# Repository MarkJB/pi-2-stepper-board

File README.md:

Copyright 2016 Mark Benson. Portions probably copyright Raspberry Pi foundation (https://github.com/raspberrypi/hats) (Specifically the HAT Spec I2C EEPROM & Back-feed circuits) so I'm not attempting to assert any Copyright over them, besides my work is licensed under Creative Commons so not sure what else I can do. I'm not a lawyer... thinking about this stuff makes my brain ache.

License: CC-BY 4.0

No warranty implied or given. Use at your own risk.

Repo branches:

Master is at v1.01b

PCBs in the wild (4) at v1.0b

* v1.0a - Pi 2/3 add-on board. Original version.
* v1.0b - Pi 2/3 HAT spec capable board. PCB follows the Pi Foundation HAT spec https://github.com/raspberrypi/hats
* v1.01b - Fixes - Swapped com port pins (Pi Tx/Rx now nearest GPIO and Arduino Tx/Rx nearest Arduino as that seems more logical) - Changed LED for Bi-colour LED, uses existing LED GPIO Pin 7 (GP4) and adds Pin 17 (GP17) - Removed plating from NTPH camera slot - Fixed front silk screen Endstop2 graphic line now points to P3.

###This is my Pi 'HAT'* drawing machine add-on board for the Raspberry Pi 2 (and later).

It can drive 2 stepper motors and a servo, has provision for end stop switches and both I2C and SPI peripherals.

Designed for use with vPiP (https://github.com/brianinnes/vpip). vPiP is a Python based vertical hanging plotter control software.

This board is a work in progress and is currently untested.

vPiP is as yet unreleased. More information as it becomes available.

I wouldn't bother making one yet...

\* 'HAT' because while the board supports the HAT spec, it would have to be assembled with the HAT spec components (the EEPROM would need to be programmed, plus a few other pyhsical additions like a specific height GPIO connector and stand-offs) to be considered a HAT without any reservations.

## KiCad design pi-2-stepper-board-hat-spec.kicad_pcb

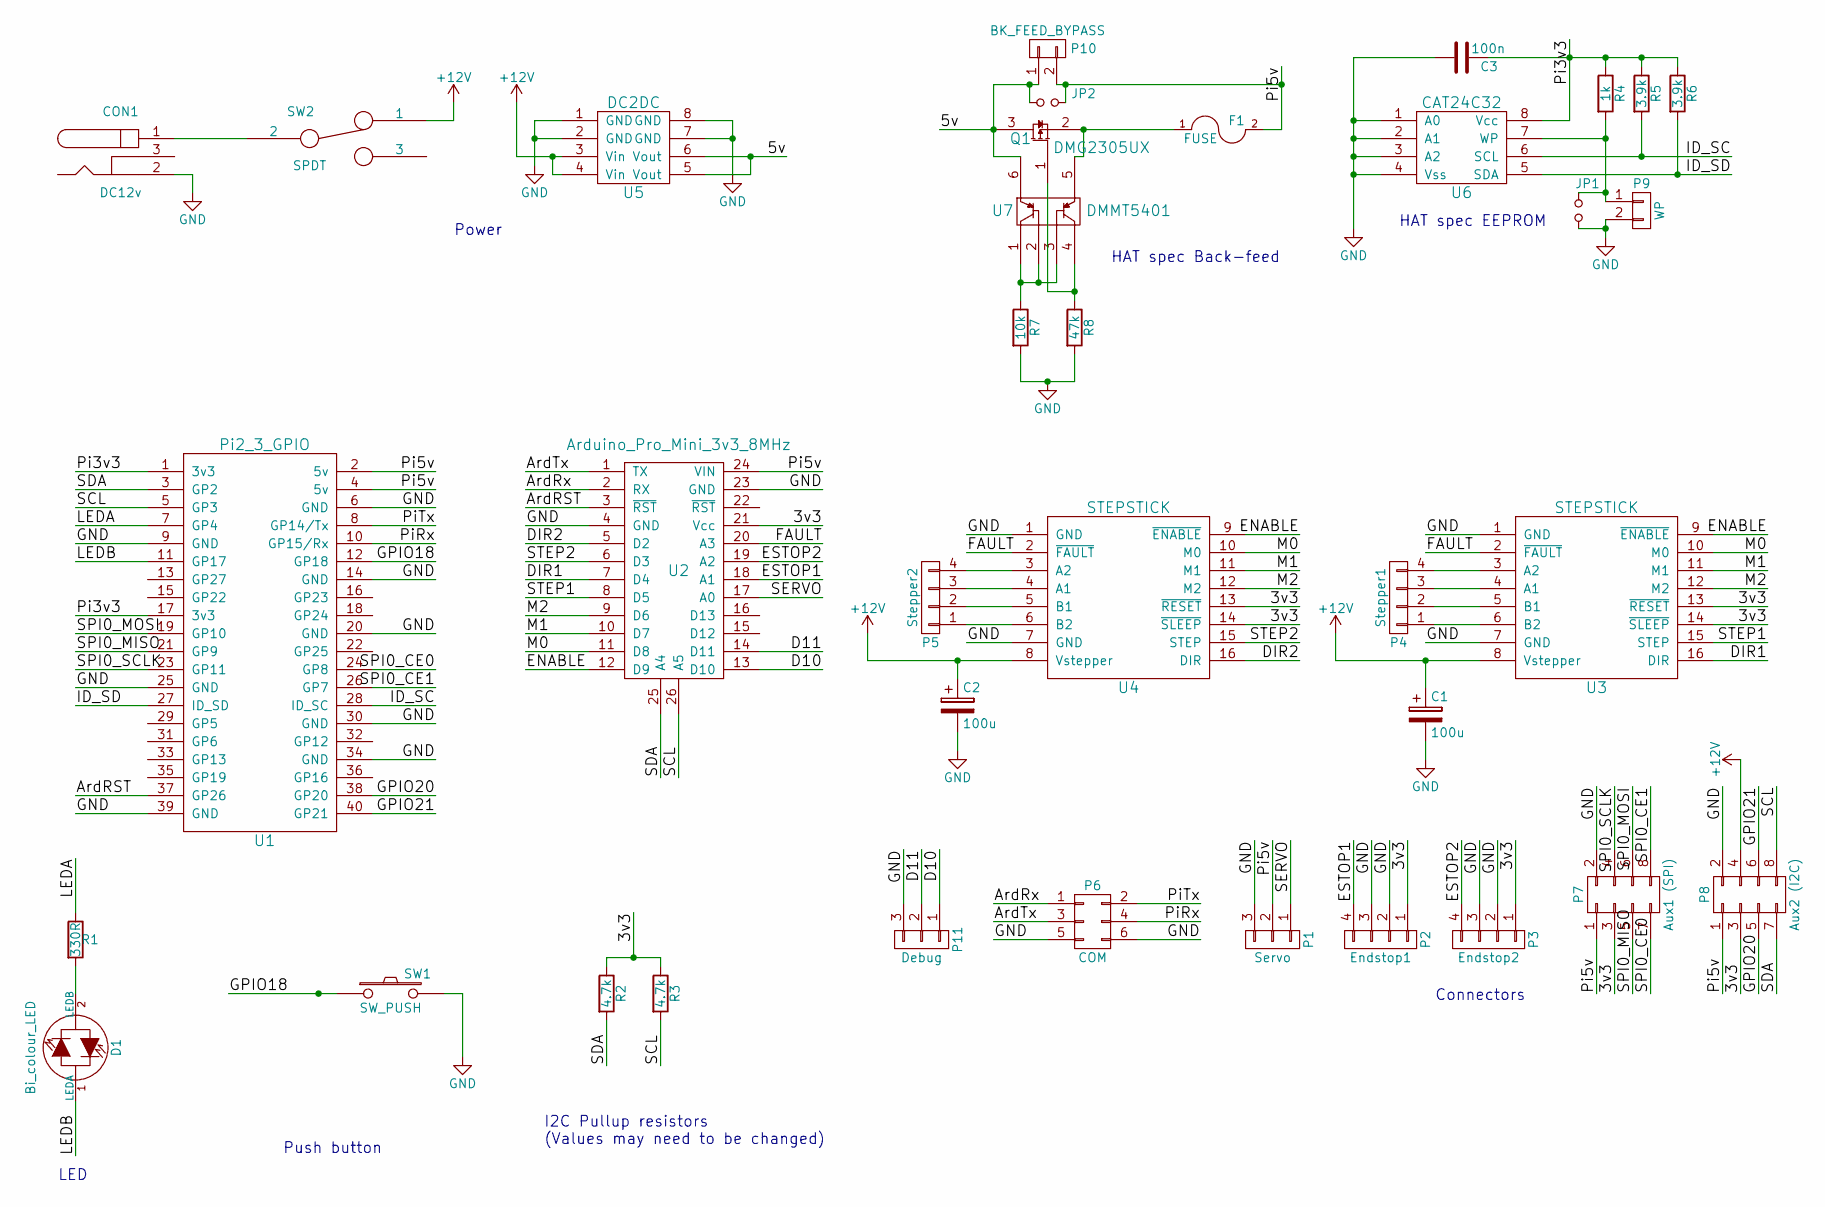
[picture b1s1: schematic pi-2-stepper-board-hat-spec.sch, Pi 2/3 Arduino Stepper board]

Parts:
C1, C2: 100u; Cap_laying_flat_2.5mm_lead_pitch
C3: 100n; C_0805
CON1: DC12v; BARREL_JACK
D1: Bi_colour_LED; LED-3MM
F1: FUSE; Fuse_SMD1206_HandSoldering
JP1, JP2: Jumper_NO_Small; Solder_Jumper
P1: Servo; Pin_Header_Straight_1x03
P2: Endstop1; Pin_Header_Straight_1x04
P3: Endstop2; Pin_Header_Straight_1x04
P4: Stepper1; Pin_Header_Straight_1x04
P5: Stepper2; Pin_Header_Straight_1x04
P6: COM; Pin_Header_Straight_2x03
P7: Aux1 (SPI); Pin_Header_Straight_2x04
P8: Aux2 (I2C); Pin_Header_Straight_2x04
P9: WP; Pin_Header_Straight_1x02
P10: BK_FEED_BYPASS; Pin_Header_Straight_1x02
P11: Debug; Pin_Header_Straight_1x03
Q1: DMG2305UX; SOT-23
R1: 330R; R1
R2, R3: 4.7k; R_0805
R4: 1k; R_0805
R5, R6: 3.9k; R_0805
R7: 10k; R_0805
R8: 47k; R_0805
SW1: SW_PUSH; TactSw
SW2: SPDT; SlideSw
U1: Pi2_3_GPIO; Pi_2_3_Hat_spec
U2: Arduino_Pro_Mini_3v3_8MHz; Arduino_Pro_Mini
U3, U4: STEPSTICK; Stepstick
U5: DC2DC; DSUN_DC2DC
U6: CAT24C32; SOIC-8_3.9x4.9mm_Pitch1.27mm
U7: DMMT5401; SOT-23-6

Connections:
+12V: C1.1, C2.1, P8.4, SW2.1, U3.8 (Vstepper), U4.8 (Vstepper), U5.3 (Vin), U5.4 (Vin)
/3v3: P2.1, P3.1, P7.3, P8.3, R2.1, R3.1, U2.21 (Vcc), U3.13 (~RESET), U3.14 (~SLEEP), U4.13 (~RESET), U4.14 (~SLEEP)
/ArdRST: U1.37 (GP26), U2.3 (~RST)
/ArdRx: P6.1, U2.2 (RX)
/ArdTx: P6.3, U2.1 (TX)
/D10: P11.1, U2.13 (D10)
/D11: P11.2, U2.14 (D11)
/DIR1: U2.7 (D4), U3.16 (DIR)
/DIR2: U2.5 (D2), U4.16 (DIR)
/ENABLE: U2.12 (D9), U3.9 (~ENABLE), U4.9 (~ENABLE)
/ESTOP1: P2.4, U2.18 (A1)
/ESTOP2: P3.4, U2.19 (A2)
/FAULT: U2.20 (A3), U3.2 (~FAULT), U4.2 (~FAULT)
/GPIO18: SW1.1, U1.12 (GP18)
/GPIO20: P8.5, U1.38 (GP20)
/GPIO21: P8.6, U1.40 (GP21)
/ID_SC: R5.2, U1.28 (ID_SC), U6.6 (SCL)
/ID_SD: R6.2, U1.27 (ID_SD), U6.5 (SDA)
/LEDA: R1.1, U1.7 (GP4)
/LEDB: D1.1 (LEDA), U1.11 (GP17)
/M0: U2.11 (D8), U3.10 (M0), U4.10 (M0)
/M1: U2.10 (D7), U3.11 (M1), U4.11 (M1)
/M2: U2.9 (D6), U3.12 (M2), U4.12 (M2)
/Pi3v3: C3.1, R4.1, R5.1, R6.1, U1.1 (3v3), U1.17 (3v3), U6.8 (Vcc)
/Pi5v: F1.2, JP2.2, P1.2, P7.1, P8.1, P10.2, U1.2 (5v), U1.4 (5v), U2.24 (VIN)
/PiRx: P6.4, U1.10 (GP15/Rx)
/PiTx: P6.2, U1.8 (GP14/Tx)
/SCL: P8.8, R3.2, U1.5 (GP3), U2.26 (A5)
/SDA: P8.7, R2.2, U1.3 (GP2), U2.25 (A4)
/SERVO: P1.1, U2.17 (A0)
/SPI0_CE0: P7.7, U1.24 (GP8)
/SPI0_CE1: P7.8, U1.26 (GP7)
/SPI0_MISO: P7.5, U1.21 (GP9)
/SPI0_MOSI: P7.6, U1.19 (GP10)
/SPI0_SCLK: P7.4, U1.23 (GP11)
/STEP1: U2.8 (D5), U3.15 (STEP)
/STEP2: U2.6 (D3), U4.15 (STEP)
unnamed: CON1.1, SW2.2
unnamed: D1.2 (LEDB), R1.2
unnamed: F1.1, Q1.2, U7.5
unnamed: JP1.1, P9.1, R4.2, U6.7 (WP)
unnamed: P4.1, U3.6 (B2)
unnamed: P4.2, U3.5 (B1)
unnamed: P4.3, U3.4 (A1)
unnamed: P4.4, U3.3 (A2)
unnamed: P5.1, U4.6 (B2)
unnamed: P5.2, U4.5 (B1)
unnamed: P5.3, U4.4 (A1)
unnamed: P5.4, U4.3 (A2)
unnamed: Q1.1, R8.1, U7.4
unnamed: R7.1, U7.1, U7.2, U7.3

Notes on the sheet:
Push button
I2C Pullup resistors (Values may need to be changed)
Power
Connectors
HAT spec EEPROM
LED
HAT spec Back-feed

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
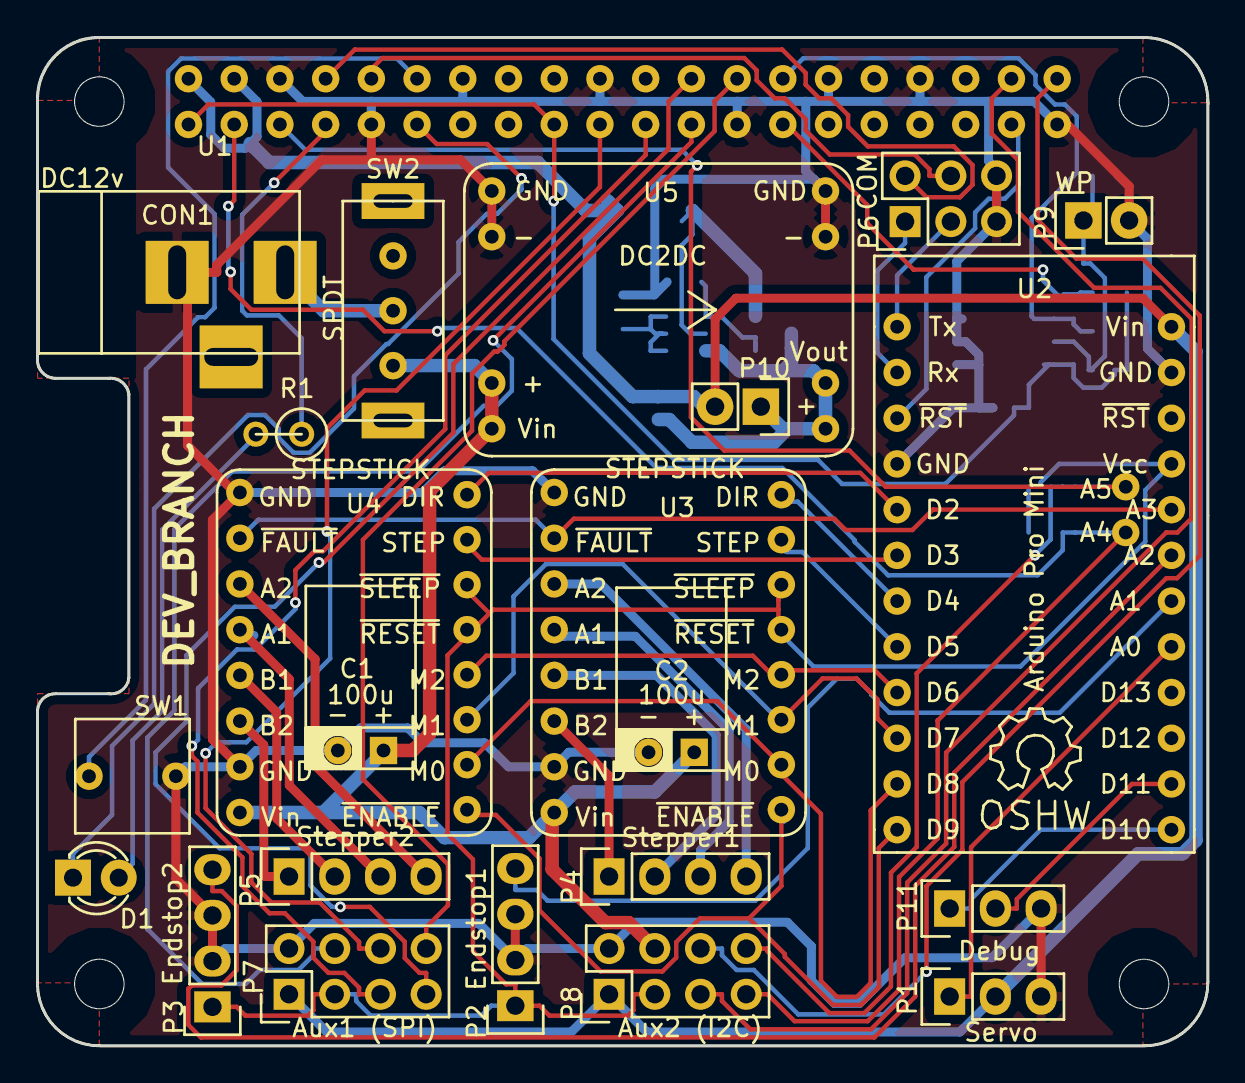
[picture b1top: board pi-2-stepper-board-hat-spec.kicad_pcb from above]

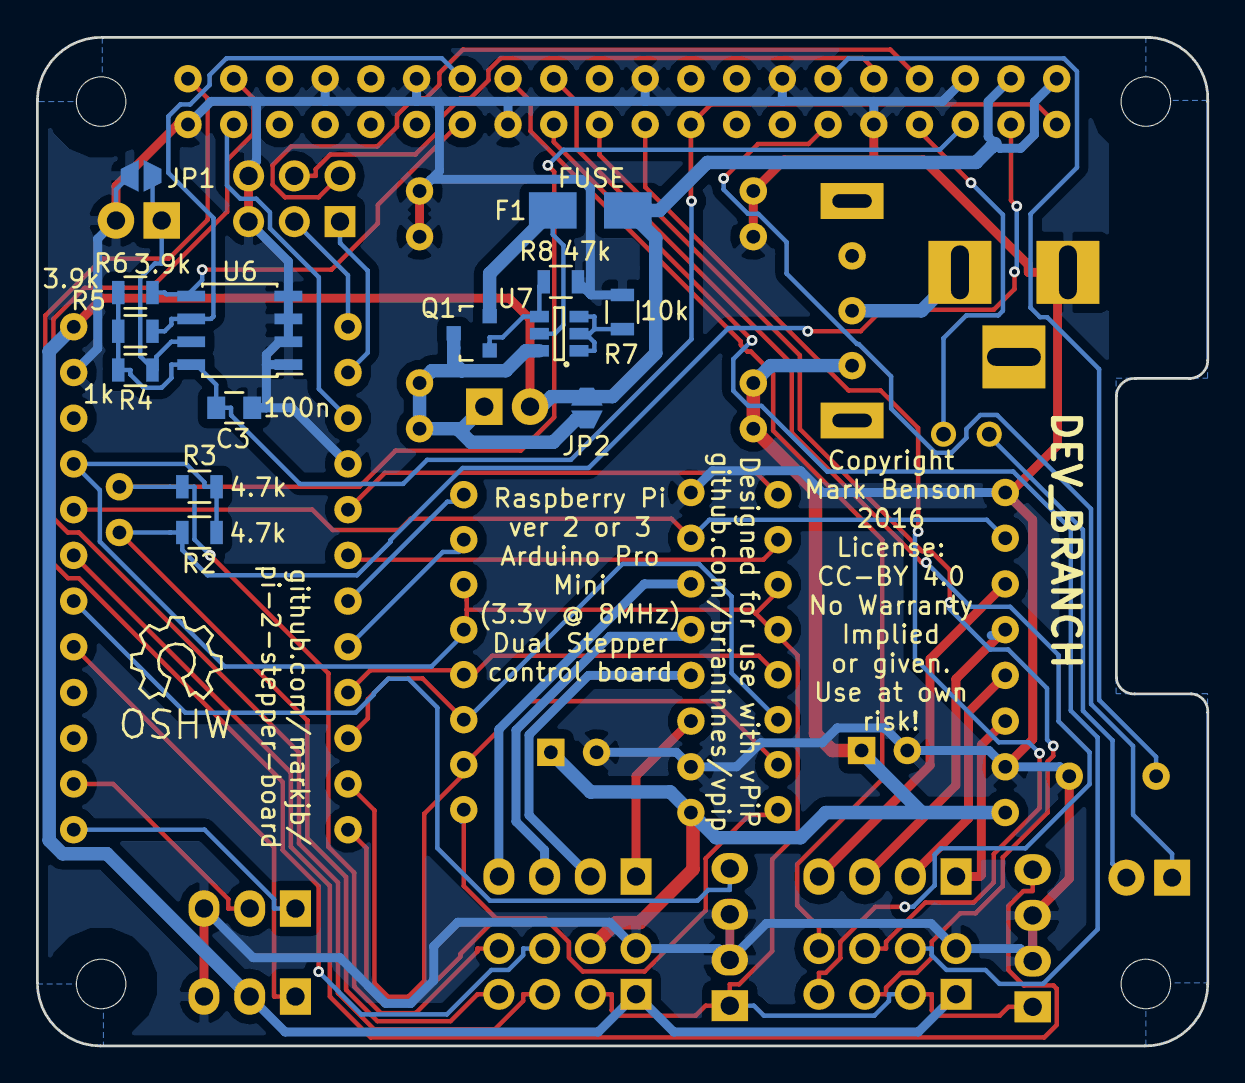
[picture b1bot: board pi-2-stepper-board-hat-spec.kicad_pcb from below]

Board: 2 copper layers, 65.0 x 56.0 mm, 39 parts (15 on the bottom side), 53 nets.

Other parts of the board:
OSH1, OSH2: Symbol_OSHW-Logo_SilkScreen

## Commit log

2016-03-14 :circus_tent: Added .gitattributes & .gitignore files
2016-03-16 Added I2C updated text
2016-03-28 Added I2C port and other fixes
2016-04-06 Design to HAT spec
    Added HAT spec board (Cable cut-outs, EEPROM, Back-feed circuit). Added
    jumpers to by-pass back-feed circuit. Fixed NPTH pads. Added LED.
    Removed push button pull-up resistor.
    NOTE: If HAT spec back-feed circuit is not fitted, Pi & Arduino are not
    powered by the DC-DC converter until either P10 or JP2 are shorted. This
    also by-passes the Poly fuse F1. Here be dragons...
2016-04-06 Added version number v1.0b
2016-04-07 Update licence version
2016-04-07 Clean up repo - board 1.0a non hat spec
2016-04-07 Clean up repo - board 1.0b hat spec
2016-04-07 Clean up repo
2016-04-07 Update image
2016-04-24 Milestone 1.01b fixes
    Swapped com port sides
    Replaced LED with Bi-colour LED
    Fixed Silkscreen & NPTH plated slot
2016-04-24 Clean up schematic
2016-04-24 Update License version
    Trying to get all the mentions of the CC-BY license to say CC-BY 4.0 as
    that is the intended license and some of the files are still a bit
    messy.
2016-04-24 Updated another instance of an incorrect license
2016-04-25 Expanded aux ports
2016-04-25 Fixed silkscreen

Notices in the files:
pi-2-stepper-board-hat-spec.kicad_pcb:
Copyright Mark Benson 2016
